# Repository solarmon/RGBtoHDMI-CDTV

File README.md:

# RGBtoHDMI-CDTV

## Introduction

This is an RGBtoHDMI solution is based on the original work by **hoglet67** and **IanSB**:

hoglet67:
https://github.com/hoglet67/RGBtoHDMI

IanSB:
https://github.com/IanSB/RGBtoHDMI

The solution is based on the RGBtoHDMI CPLD based hardware design by **LinuxJedi**:

https://github.com/LinuxJedi/AmigaRGBtoHDMI

Special mention to **c0pperdragon** for the original RGBtoHDMI board solution for the Amiga:

https://github.com/c0pperdragon/Amiga-Digital-Video

## Wiki

Please see the [wiki](https://github.com/solarmon/RGBtoHDMI-CDTV/wiki) for further details:

* [RGBtoHDMI CDTV Quick Start Guide](https://github.com/solarmon/RGBtoHDMI-CDTV/wiki/RGBtoHDMI-CDTV-Quick-Start-Guide)
* [RGBtoHDMI CDTV BoM](https://github.com/solarmon/RGBtoHDMI-CDTV/wiki/RGBtoHDMI-CDTV-BoM)
* [RGBtoHDMI CDTV Build Guide](https://github.com/solarmon/RGBtoHDMI-CDTV/wiki/RGBtoHDMI-CDTV-Build-Guide)

## Support

Please raise a [support ticket](https://github.com/solarmon/RGBtoHDMI-CDTV/issues) for any issues with this project content and design files.

## Solution

This RGBtoHDMI solution has been designed to fit in to the **Video Slot** of a **Commodore CDTV**. It replaces the existing RF and composite video card, as well as providing a **bypass** for the video signals to go to the **RGB** video port.

A breakout board is used to send the digital RGB signals from the Denise video chip, over a 18-pin FFC flex cable, to the main RGBtoHDMI board sitting in the Video Slot.

The mini HDMI connector of the **Raspberry Pi Zero** is presented directly on the face plate, along with three push buttons to control the RGBtoHDMI **OSD** menu.

This LinuxJedi CPLD based version supports either **OCS** or **ECS** Denise. There is no jumper required - you just need to make sure you **auto-calibrate** it using the OSD menu.

As with all the other RGBtoHDMI solution, **audio over HDMI** is currently **NOT supported**. This board does have breakout points for the **AUDL** and **AUDR** but is not used.

(...yes, I know the serial port and LEDs are missing in this picture! Oops!)

## Design

### RGBtoHDMI CDTV Main Board

Design files: https://github.com/solarmon/RGBtoHDMI-CDTV/tree/main/RGBtoHDMI%20Amiga%20Denise%20CPLD%20FFC%20-%20CDTV%20Video%20Slot

### RGBtoHDMI CDTV Face Plate

Design files: https://github.com/solarmon/RGBtoHDMI-CDTV/tree/main/RGBtoHDMI%20Amiga%20Denise%20CPLD%20FFC%20-%20CDTV%20Video%20Slot

The face plate for the RGBtoHDMI CDTV board is also a PCB. It is attached to the main board using guide slots that has solder pads so that it can be soldered together.

### RGBtoHDMI CDTV Denise Breakout board v1

Design files: https://github.com/solarmon/RGBtoHDMI-CDTV/tree/main/RGBtoHDMI%20Amiga%20Denise%20DIP%20Breakout%20FFC%20-%20CDTV

### RGBtoHDMI CDTV Denise Breakout board v2

Design files: https://github.com/solarmon/RGBtoHDMI-CDTV/tree/main/RGBtoHDMI%20Amiga%20Denise%20DIP%20Breakout%20FFC%20-%20CDTV%20v2

The v2 breakout board has a lower profile by using female round pins that act both as the socket for the Denise chip, as well as the pin to go in to the Denise socket on the CDTV.

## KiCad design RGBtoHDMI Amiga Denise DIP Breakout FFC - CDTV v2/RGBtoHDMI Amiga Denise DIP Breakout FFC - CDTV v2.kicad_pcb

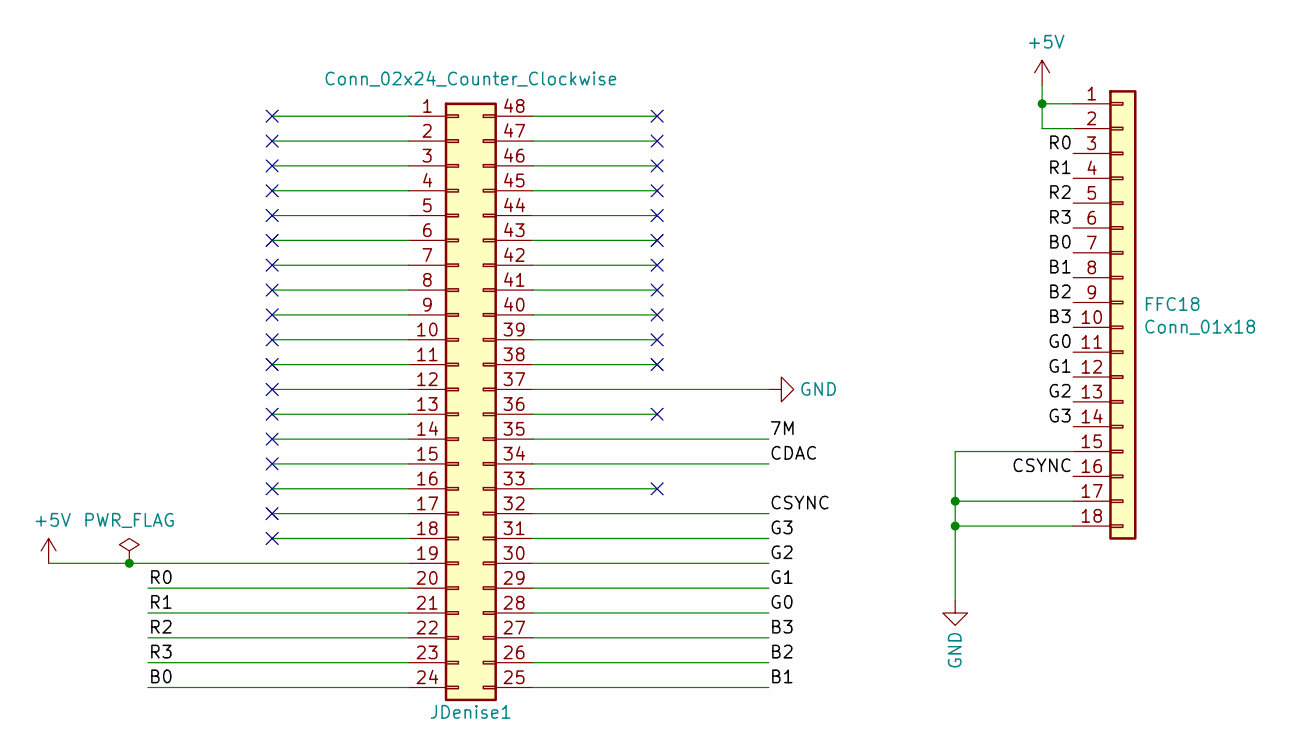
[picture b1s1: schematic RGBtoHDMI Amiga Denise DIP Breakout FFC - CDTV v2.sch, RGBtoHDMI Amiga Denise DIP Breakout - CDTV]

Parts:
FFC18: Conn_01x18; FPC-SMD_X10B25U18T
JDenise1: Conn_02x24_Counter_Clockwise; DIP-48_W15.24mm_Socket_Turned_Pins

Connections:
+5V: FFC18.1, FFC18.2, JDenise1.19
/7M: JDenise1.35
/B0: FFC18.7, JDenise1.24
/B1: FFC18.8, JDenise1.25
/B2: FFC18.9, JDenise1.26
/B3: FFC18.10, JDenise1.27
/CDAC: JDenise1.34
/CSYNC: FFC18.16, JDenise1.32
/G0: FFC18.11, JDenise1.28
/G1: FFC18.12, JDenise1.29
/G2: FFC18.13, JDenise1.30
/G3: FFC18.14, JDenise1.31
/R0: FFC18.3, JDenise1.20
/R1: FFC18.4, JDenise1.21
/R2: FFC18.5, JDenise1.22
/R3: FFC18.6, JDenise1.23
GND: FFC18.15, FFC18.17, FFC18.18, FFC18.MP, JDenise1.37

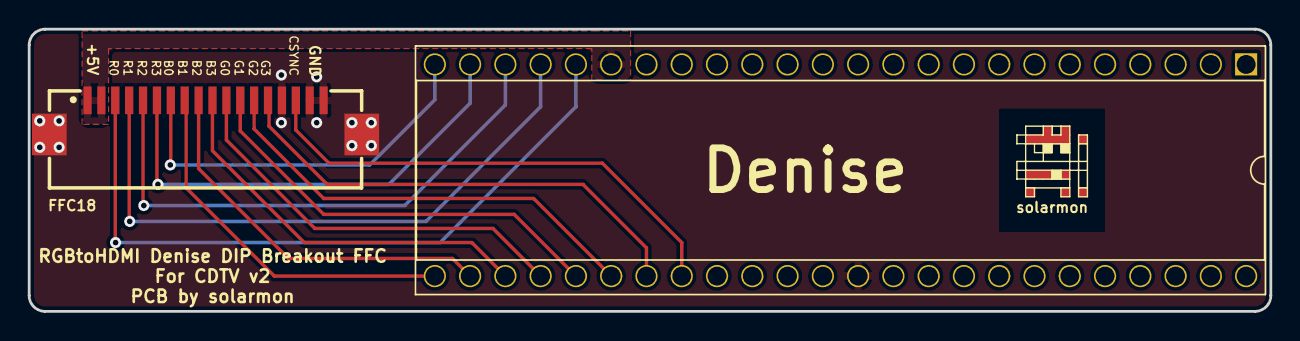
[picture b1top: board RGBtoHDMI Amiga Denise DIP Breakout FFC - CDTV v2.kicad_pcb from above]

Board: 2 copper layers, 89.4 x 20.3 mm, 3 parts (0 on the bottom side), 15 nets.

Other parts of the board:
solarmon: solarmon-logo-25mils

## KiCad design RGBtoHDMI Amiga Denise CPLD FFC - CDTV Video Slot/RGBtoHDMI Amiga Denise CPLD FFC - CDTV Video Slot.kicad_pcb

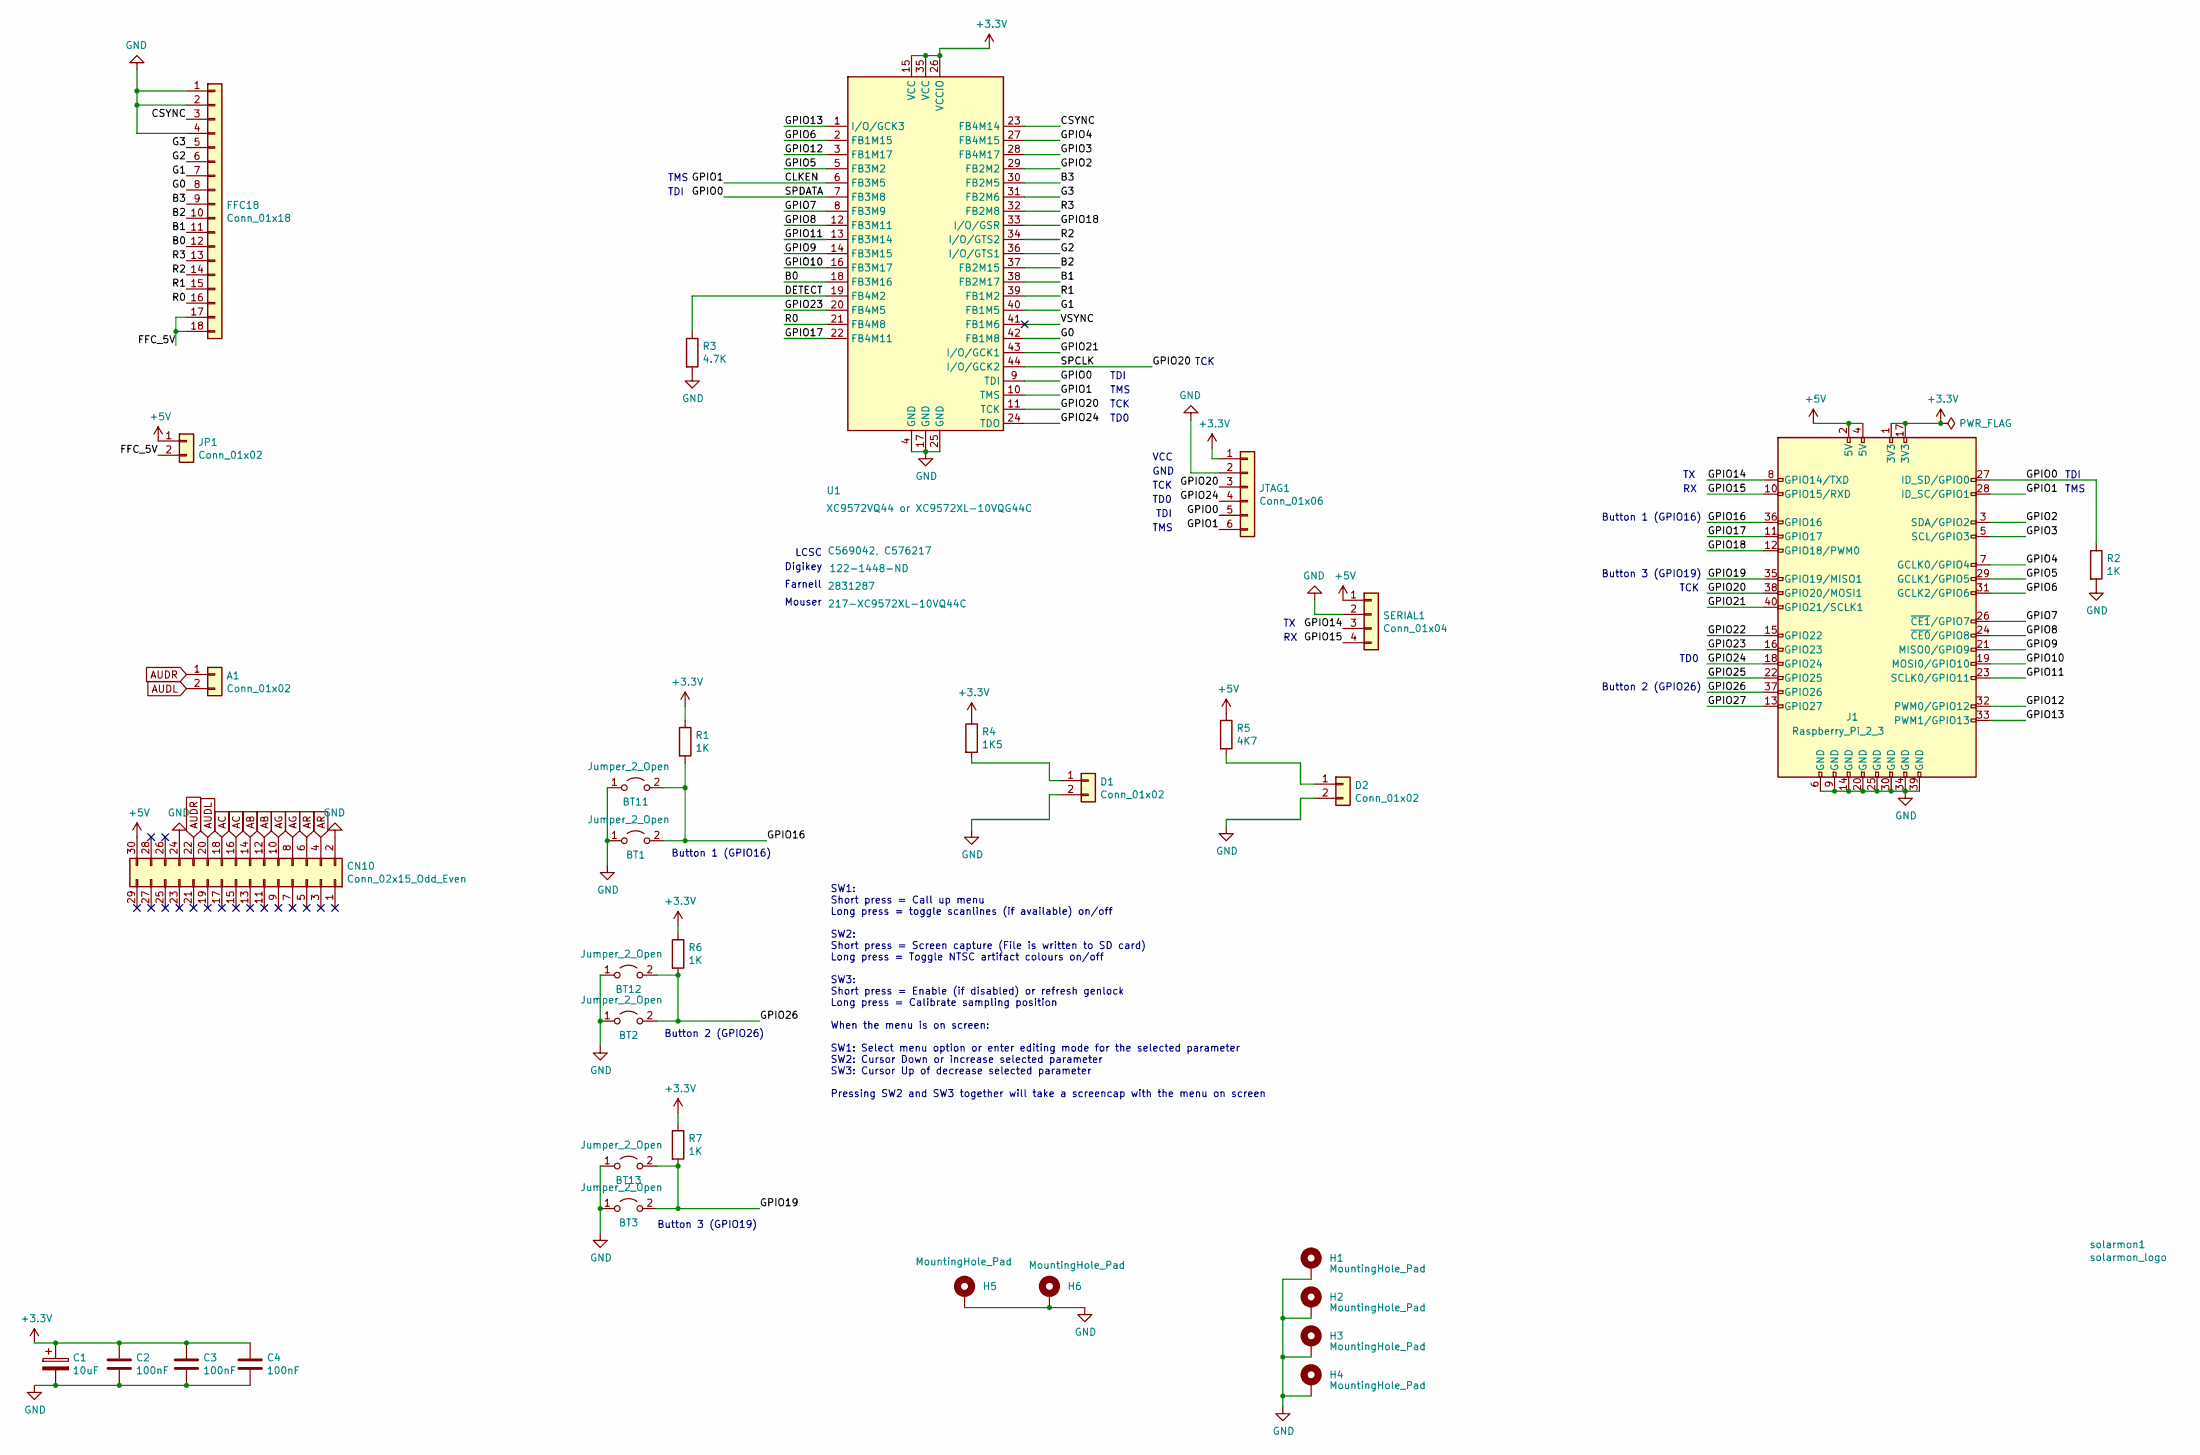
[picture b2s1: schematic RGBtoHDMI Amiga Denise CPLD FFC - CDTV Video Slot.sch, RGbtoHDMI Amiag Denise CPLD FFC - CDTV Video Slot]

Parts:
A1: Conn_01x02; PinHeader_1x02_P2.54mm_Vertical
BT1, BT2, BT3: Jumper_2_Open; PinHeader_1x02_P2.54mm_Vertical
BT11, BT12, BT13: Jumper_2_Open; PUSH_BUTTON_RIGHT_ANGLE
C1: 10uF; C_0805_2012Metric_Pad1.18x1.45mm_HandSolder
C2, C3, C4: 100nF; C_0805_2012Metric_Pad1.18x1.45mm_HandSolder
CN10: Conn_02x15_Odd_Even; CDTV_Video_Slot_30_pin
D1, D2: Conn_01x02; PinHeader_1x02_P2.54mm_Vertical
FFC18: Conn_01x18; FPC-SMD_X10B25U18T
H1, H2, H3, H4: MountingHole_Pad; MountingHole_2.5mm_Pad_Via
H5, H6: MountingHole_Pad; MountingHole_3.2mm_M3
J1: Raspberry_Pi_2_3; PinSocket_2x20_P2.54mm_Vertical
JP1: Conn_01x02; PinHeader_1x02_P2.54mm_Horizontal
JTAG1: Conn_01x06; PinHeader_1x06_P2.54mm_Vertical
R1, R2, R6, R7: 1K; R_0805_2012Metric_Pad1.20x1.40mm_HandSolder
R3: 4.7K; R_0805_2012Metric_Pad1.20x1.40mm_HandSolder
R4: 1K5; R_0805_2012Metric_Pad1.20x1.40mm_HandSolder
R5: 4K7; R_0805_2012Metric_Pad1.20x1.40mm_HandSolder
SERIAL1: Conn_01x04; PinHeader_1x04_P2.54mm_Horizontal
U1: XC9572VQ44 or XC9572XL-10VQG44C; TQFP-44_10x10mm_P0.8mm; LCSC C569042, C576217
solarmon1: solarmon_logo; solarmon-logo-25mils

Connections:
+3V3: C1.1, C2.1, C3.1, C4.1, J1.1 (3V3), J1.17 (3V3), JTAG1.1, R1.1, R4.1, R6.1, R7.1, U1.15 (VCC), U1.26 (VCCIO), U1.35 (VCC)
+5V: CN10.30, J1.2 (5V), J1.4 (5V), JP1.1, R5.1, SERIAL1.1
/B0: FFC18.12, U1.18 (FB3M16)
/B1: FFC18.11, U1.38 (FB2M17)
/B2: FFC18.10, U1.37 (FB2M15)
/B3: FFC18.9, U1.30 (FB2M5)
/CLKEN: J1.28 (ID_SC/GPIO1), JTAG1.6, U1.6 (FB3M5), U1.10 (TMS)
/CSYNC: FFC18.3, U1.23 (FB4M14)
/DETECT: R3.1, U1.19 (FB4M2)
/FFC_5V: FFC18.17, FFC18.18, JP1.2
/G0: FFC18.8, U1.42 (FB1M8)
/G1: FFC18.7, U1.40 (FB1M5)
/G2: FFC18.6, U1.36 (I/O/GTS1)
/G3: FFC18.5, U1.31 (FB2M6)
/GPIO0: J1.27 (ID_SD/GPIO0), JTAG1.5, R2.1, U1.7 (FB3M8), U1.9 (TDI)
/GPIO2: J1.3 (SDA/GPIO2), U1.29 (FB2M2)
/GPIO3: J1.5 (SCL/GPIO3), U1.28 (FB4M17)
/GPIO4: J1.7 (GCLK0/GPIO4), U1.27 (FB4M15)
/GPIO5: J1.29 (GCLK1/GPIO5), U1.5 (FB3M2)
/GPIO6: J1.31 (GCLK2/GPIO6), U1.2 (FB1M15)
/GPIO7: J1.26 (~CE1~/GPIO7), U1.8 (FB3M9)
/GPIO8: J1.24 (~CE0~/GPIO8), U1.12 (FB3M11)
/GPIO9: J1.21 (MISO0/GPIO9), U1.14 (FB3M15)
/GPIO10: J1.19 (MOSI0/GPIO10), U1.16 (FB3M17)
/GPIO11: J1.23 (SCLK0/GPIO11), U1.13 (FB3M14)
/GPIO12: J1.32 (PWM0/GPIO12), U1.3 (FB1M17)
/GPIO13: J1.33 (PWM1/GPIO13), U1.1 (I/O/GCK3)
/GPIO14: J1.8 (GPIO14/TXD), SERIAL1.3
/GPIO15: J1.10 (GPIO15/RXD), SERIAL1.4
/GPIO16: BT1.2 (B), BT11.2 (B), J1.36 (GPIO16), R1.2
/GPIO17: J1.11 (GPIO17), U1.22 (FB4M11)
/GPIO18: J1.12 (GPIO18/PWM0), U1.33 (I/O/GSR)
/GPIO19: BT3.2 (B), BT13.2 (B), J1.35 (GPIO19/MISO1), R7.2
/GPIO20: J1.38 (GPIO20/MOSI1), JTAG1.3, U1.11 (TCK), U1.44 (I/O/GCK2)
/GPIO21: J1.40 (GPIO21/SCLK1), U1.43 (I/O/GCK1)
/GPIO22: J1.15 (GPIO22)
/GPIO23: J1.16 (GPIO23), U1.20 (FB4M5)
/GPIO24: J1.18 (GPIO24), JTAG1.4, U1.24 (TDO)
/GPIO25: J1.22 (GPIO25)
/GPIO26: BT2.2 (B), BT12.2 (B), J1.37 (GPIO26), R6.2
/GPIO27: J1.13 (GPIO27)
/R0: FFC18.16, U1.21 (FB4M8)
/R1: FFC18.15, U1.39 (FB1M2)
/R2: FFC18.14, U1.34 (I/O/GTS2)
/R3: FFC18.13, U1.32 (FB2M8)
/VSYNC: U1.41 (FB1M6)
AB: CN10.12, CN10.14
AC: CN10.16, CN10.18
AG: CN10.8, CN10.10
AR: CN10.4, CN10.6
AUDL: A1.2, CN10.20
AUDR: A1.1, CN10.22
GND: BT1.1 (A), BT2.1 (A), BT3.1 (A), BT11.1 (A), BT12.1 (A), BT13.1 (A), C1.2, C2.2, C3.2, C4.2, CN10.2, CN10.24, D1.2, D2.2, FFC18.1, FFC18.2, FFC18.4, FFC18.MP, H1.1, H2.1, H3.1, H4.1, H5.1, H6.1, J1.6 (GND), J1.9 (GND), J1.14 (GND), J1.20 (GND), J1.25 (GND), J1.30 (GND), J1.34 (GND), J1.39 (GND), JTAG1.2, R2.2, R3.2, SERIAL1.2, U1.4 (GND), U1.17 (GND), U1.25 (GND)
unnamed: D1.1, R4.2
unnamed: D2.1, R5.2

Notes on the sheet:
TCK
TMS
TDI
TD0
GND
VCC
Button 1 (GPIO16)
Button 2 (GPIO26)
Button 3 (GPIO19)
Farnell
Digikey
LCSC
Mouser
SW1: Short press = Call up menu Long press = toggle scanlines (if available) on/off SW2: Short press = Screen capture (File is written to SD card) Long press = Toggle NTSC artifact colours on/off SW3: Short press = Enable (if disabled) or refresh genlock Long press = Calibrate sampling position Whe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

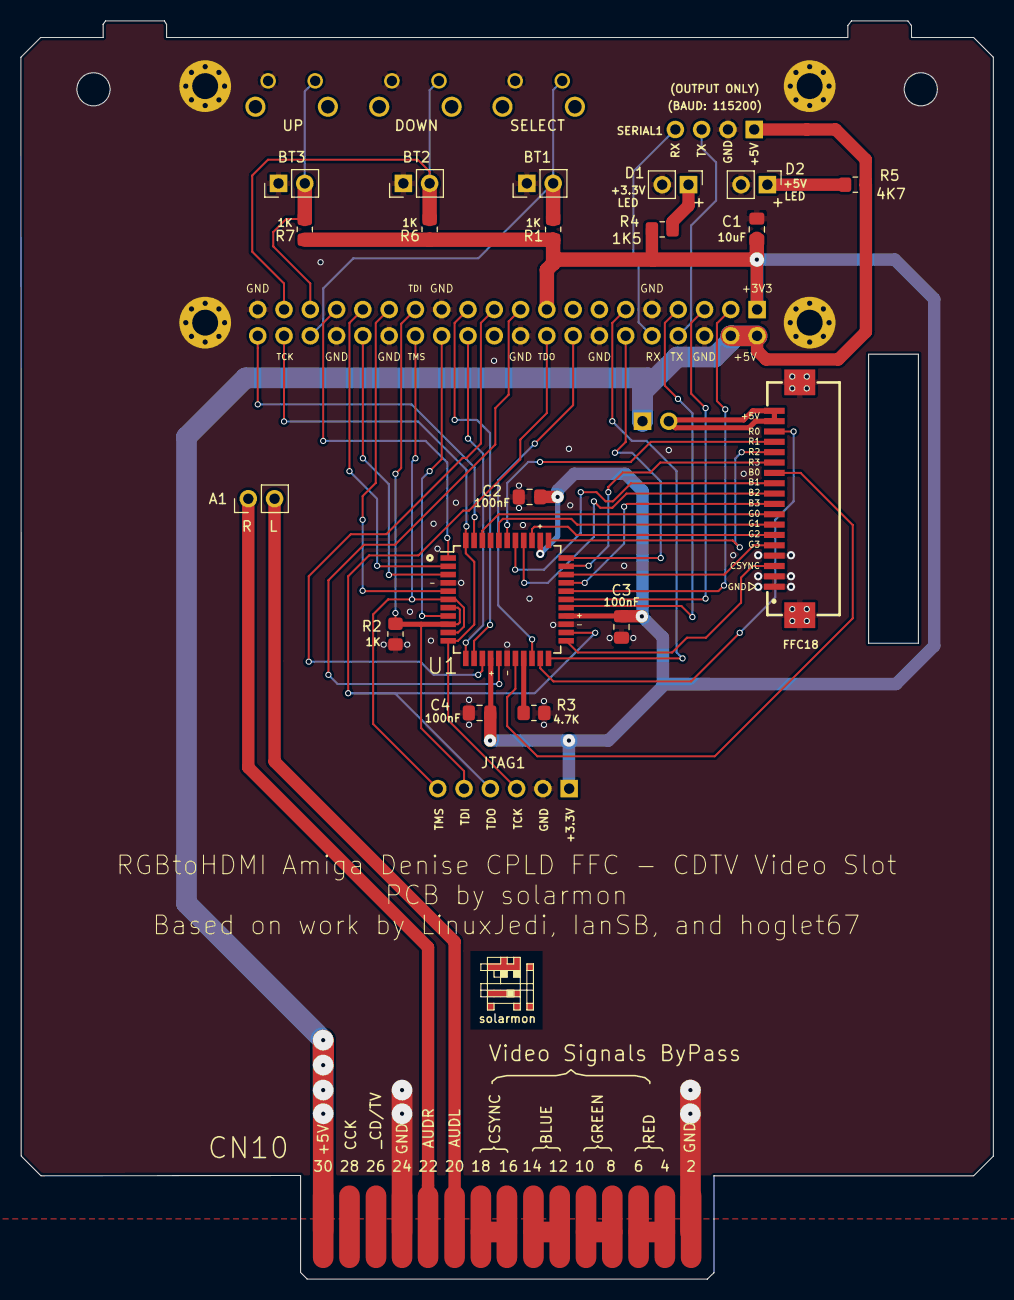
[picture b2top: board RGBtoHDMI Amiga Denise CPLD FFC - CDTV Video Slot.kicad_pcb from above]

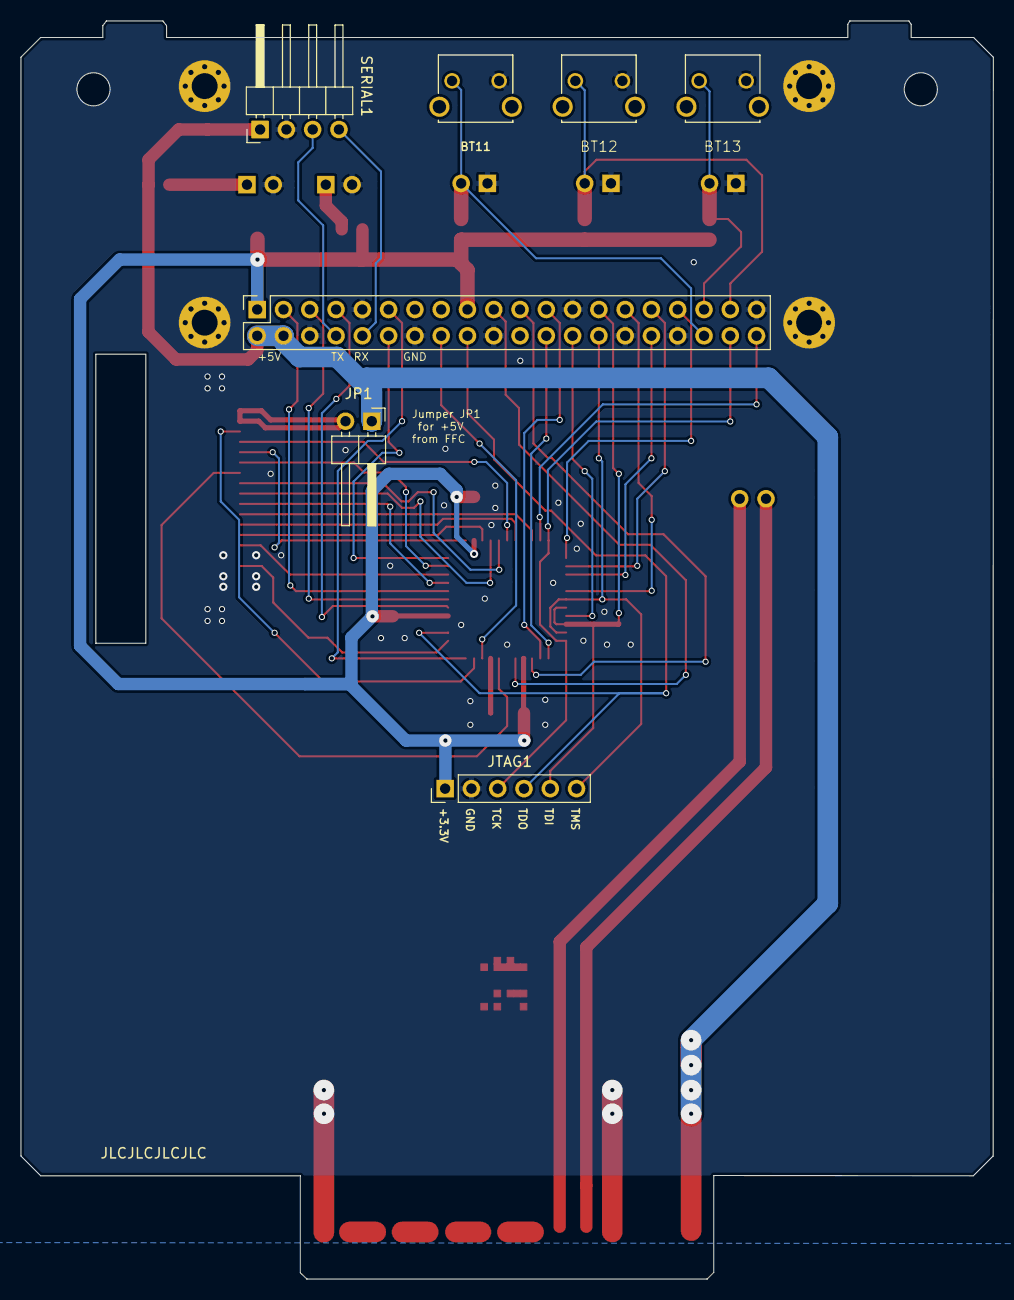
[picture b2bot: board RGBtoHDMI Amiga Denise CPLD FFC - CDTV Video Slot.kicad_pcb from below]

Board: 2 copper layers, 94.0 x 121.6 mm, 34 parts (7 on the bottom side), 51 nets.

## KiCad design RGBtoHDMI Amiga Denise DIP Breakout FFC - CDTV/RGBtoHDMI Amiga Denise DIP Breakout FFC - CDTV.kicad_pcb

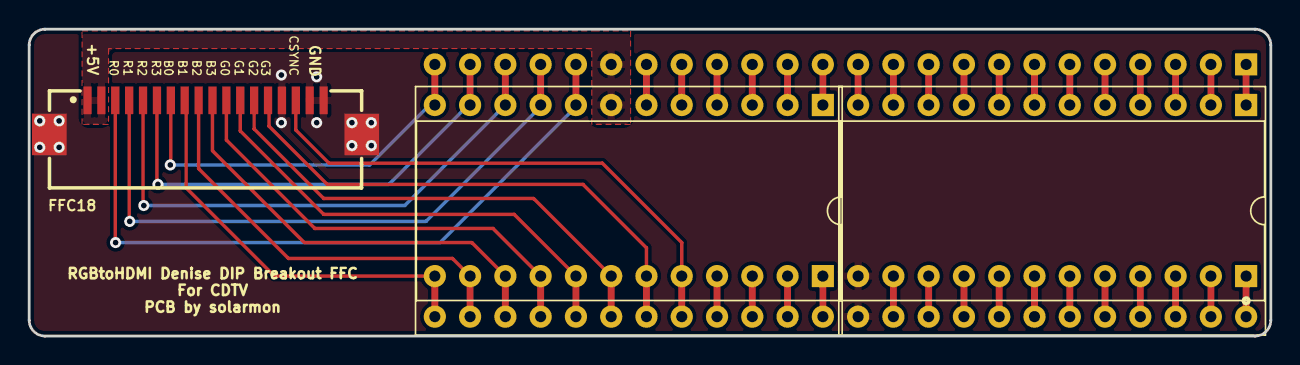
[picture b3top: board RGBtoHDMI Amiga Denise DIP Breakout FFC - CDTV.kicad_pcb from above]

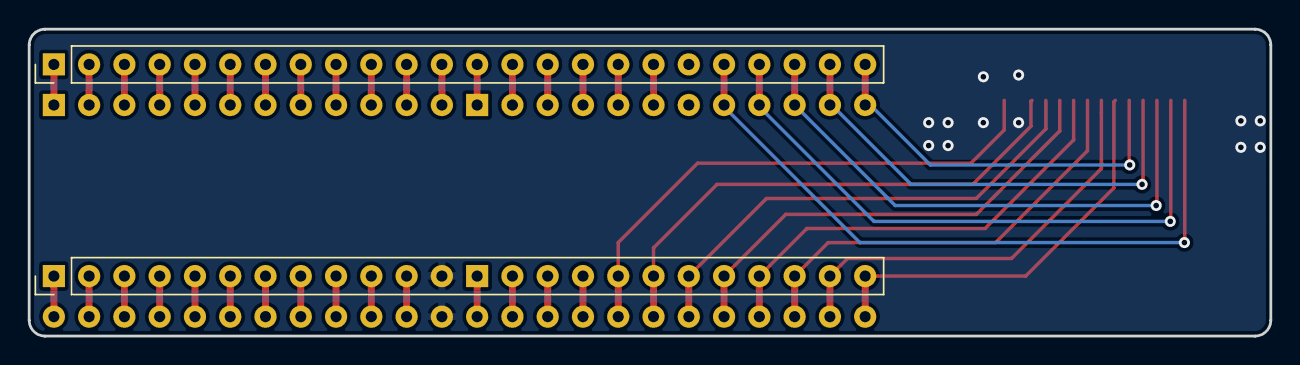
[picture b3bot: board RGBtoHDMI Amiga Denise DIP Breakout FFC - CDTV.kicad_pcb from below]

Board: 2 copper layers, 89.4 x 22.1 mm, 5 parts (2 on the bottom side), 48 nets.

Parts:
FFC18: Conn_01x18; FPC-SMD_X10B25U18T
JDenise1, JDenise2: Conn_02x12_Counter_Clockwise; DIP-24_W15.24mm_Socket
JMainBoard1, JMainBoard2: Conn_01x24; PinHeader_1x24_P2.54mm_Vertical_smaller

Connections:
+5V: FFC18.1, FFC18.2, JDenise2.7, JMainBoard1.19
/7M: JDenise2.23, JMainBoard2.14
/B0: FFC18.7, JDenise2.12, JMainBoard1.24
/B1: FFC18.8, JDenise2.13, JMainBoard2.24
/B2: FFC18.9, JDenise2.14, JMainBoard2.23
/B3: FFC18.10, JDenise2.15, JMainBoard2.22
/CDAC: JDenise2.22, JMainBoard2.15
/CSYNC: FFC18.16, JDenise2.20, JMainBoard2.17
/G0: FFC18.11, JDenise2.16, JMainBoard2.21
/G1: FFC18.12, JDenise2.17, JMainBoard2.20
/G2: FFC18.13, JDenise2.18, JMainBoard2.19
/G3: FFC18.14, JDenise2.19, JMainBoard2.18
/R0: FFC18.3, JDenise2.8, JMainBoard1.20
/R1: FFC18.4, JDenise2.9, JMainBoard1.21
/R2: FFC18.5, JDenise2.10, JMainBoard1.22
/R3: FFC18.6, JDenise2.11, JMainBoard1.23
GND: FFC18.15, FFC18.17, FFC18.18, FFC18.MP, JDenise1.13, JMainBoard2.12
unnamed: JDenise1.1, JMainBoard1.1
unnamed: JDenise1.2, JMainBoard1.2
unnamed: JDenise1.3, JMainBoard1.3
unnamed: JDenise1.4, JMainBoard1.4
unnamed: JDenise1.5, JMainBoard1.5
unnamed: JDenise1.6, JMainBoard1.6
unnamed: JDenise1.7, JMainBoard1.7
unnamed: JDenise1.8, JMainBoard1.8
unnamed: JDenise1.9, JMainBoard1.9
unnamed: JDenise1.10, JMainBoard1.10
unnamed: JDenise1.11, JMainBoard1.11
unnamed: JDenise1.12, JMainBoard1.12
unnamed: JDenise1.14, JMainBoard2.11
unnamed: JDenise1.15, JMainBoard2.10
unnamed: JDenise1.16, JMainBoard2.9
unnamed: JDenise1.17, JMainBoard2.8
unnamed: JDenise1.18, JMainBoard2.7
unnamed: JDenise1.19, JMainBoard2.6
unnamed: JDenise1.20, JMainBoard2.5
unnamed: JDenise1.21, JMainBoard2.4
unnamed: JDenise1.22, JMainBoard2.3
unnamed: JDenise1.23, JMainBoard2.2
unnamed: JDenise1.24, JMainBoard2.1
unnamed: JDenise2.1, JMainBoard1.13
unnamed: JDenise2.2, JMainBoard1.14
unnamed: JDenise2.3, JMainBoard1.15
unnamed: JDenise2.4, JMainBoard1.16
unnamed: JDenise2.5, JMainBoard1.17
unnamed: JDenise2.6, JMainBoard1.18
unnamed: JDenise2.21, JMainBoard2.16
unnamed: JDenise2.24, JMainBoard2.13

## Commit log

2021-11-16 Added KiCAD files
2021-11-16 Added KiCAD files for CDTV Denise breakout
2021-12-05 Tweaks
2021-12-05 Added installation pictures
2021-12-06 Added L+R audio points
2021-12-06 Picture edits
2021-12-10 Added RGBtoHDMI Amiga Denise DIP Breakout FFC - CDTV v2
2021-12-10 Added more pictures
2021-12-11 Added LED install guide pictures
2021-12-11 Added rounded corners pictures
2021-12-19 Added chamfered CN10 edge diagram
